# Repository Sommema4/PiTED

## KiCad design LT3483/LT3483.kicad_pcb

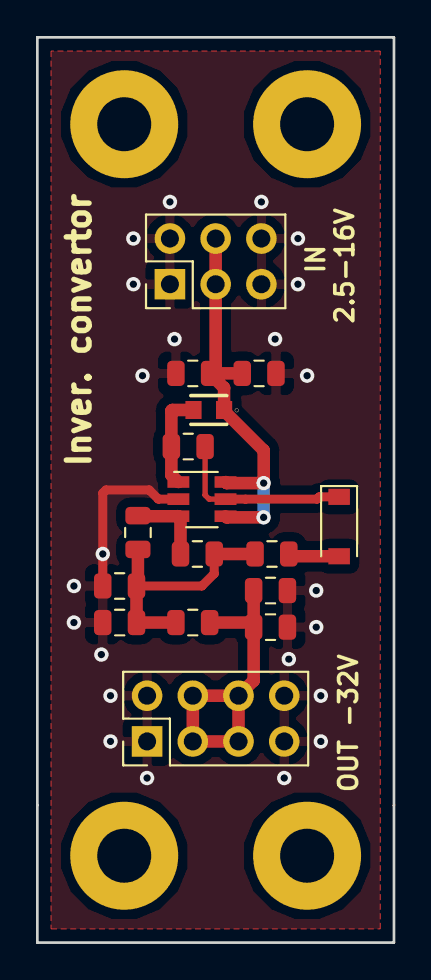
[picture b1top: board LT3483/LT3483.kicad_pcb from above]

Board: 2 copper layers, 19.8 x 50.3 mm, 20 parts (0 on the bottom side), 8 nets.

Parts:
C1: 4.7uF/30V; C_0805_2012Metric
C2: 100nF/30V; C_0805_2012Metric
C3: 0.1uF/50V; C_0805_2012Metric
C4: 5pF/50V; C_0805_2012Metric
C5, C8: 1uF/50V; C_0805_2012Metric
C6, C7: 100nF; C_0805_2012Metric
D1: MBR0540; D_SOD-123
J1: Conn_02x03_Odd_Even; PinHeader_2x03_P2.54mm_Vertical
J2: Conn_02x04_Odd_Even; PinHeader_2x04_P2.54mm_Vertical
L1: LQH2MCN100K02L
MH1: M1; MountingHole_3mm_Pad
MH2: M2; MountingHole_3mm_Pad
MH3: M3; MountingHole_3mm_Pad
MH4: M4; MountingHole_3mm_Pad
R1: 39.2R; R_0805_2012Metric
R2: 3.24M; R_0805_2012Metric
R3: 100R; R_0805_2012Metric
U1: LT3483; TSOT-23-6

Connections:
GND: C1.1, C2.1, C5.2, C6.2, C7.2, C8.2, J1.1, J1.2, J1.5, J1.6, J2.1, J2.2, J2.7, J2.8, U1.2
unnamed: C1.2, C2.2, J1.3, J1.4, L1.1, U1.4, U1.6
unnamed: C3.1, L1.2, U1.1
unnamed: C3.2, D1.1, U1.5
unnamed: C4.1, C5.1, C6.1, R1.2, R2.2, R3.2
unnamed: C4.2, R2.1, U1.3
unnamed: C7.1, C8.1, J2.3, J2.4, J2.5, J2.6, R3.1
unnamed: D1.2, R1.1

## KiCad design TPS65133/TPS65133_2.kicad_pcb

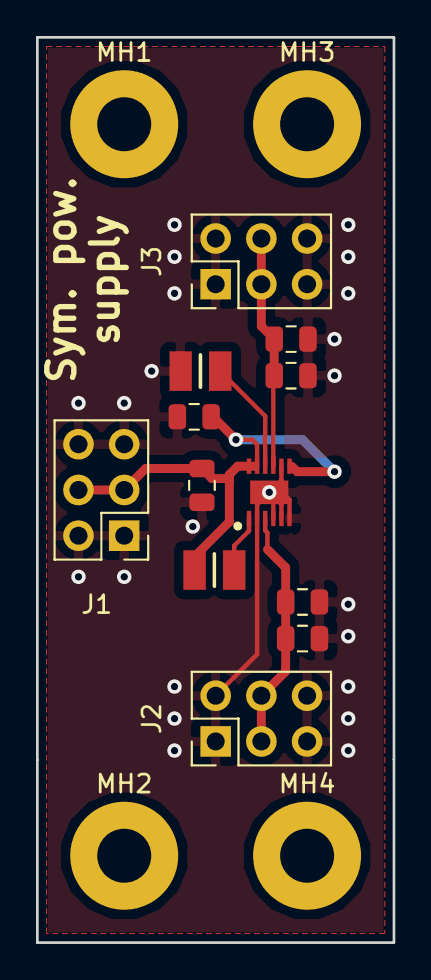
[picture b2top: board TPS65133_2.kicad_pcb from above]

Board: 2 copper layers, 19.8 x 50.3 mm, 16 parts (0 on the bottom side), 6 nets.

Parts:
C1, C5, C6: 0.1uF; C_0805_2012Metric
C2, C3, C4: 10uF; C_0805_2012Metric
IC1: TPS65133DPDR; SON45P300X300X80-13N-D
J1, J2, J3: Conn_02x03_Odd_Even; PinHeader_2x03_P2.54mm_Vertical
L1, L2: 1239AS-H-4R7M=P2
MH1, MH2, MH3, MH4: MountingHole_Pad; MountingHole_3mm_Pad

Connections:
GND: C1.2, C2.2, C3.2, C4.2, C5.2, C6.2, IC1.2, IC1.4, IC1.5, IC1.6, IC1.8, IC1.13, J1.1, J1.2, J1.5, J1.6, J2.1, J2.2, J2.5, J2.6, J3.1, J3.2, J3.5, J3.6, L2.2
unnamed: C1.1, C3.1, IC1.7, IC1.11, IC1.12, J1.3, J1.4, L1.2
unnamed: C2.1, C5.1, IC1.3, J2.3, J2.4
unnamed: C4.1, C6.1, IC1.9, J3.3, J3.4
unnamed: IC1.1, L1.1
unnamed: IC1.10, L2.1

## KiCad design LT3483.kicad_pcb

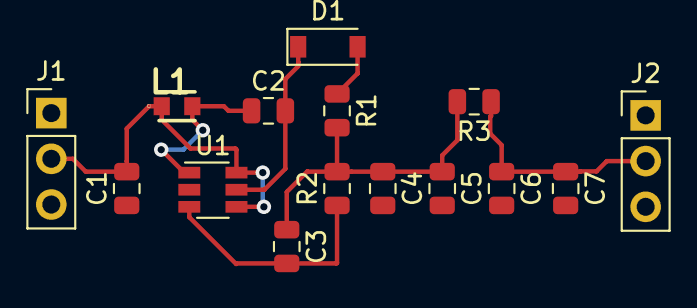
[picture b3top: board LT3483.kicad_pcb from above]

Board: 2 copper layers, 15 parts (0 on the bottom side), 8 nets.

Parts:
C1: 4.7uF/10V; C_0805_2012Metric
C2, C5, C6: 0.1uF/50V; C_0805_2012Metric
C3: 5pF/50V; C_0805_2012Metric
C4, C7: 1uF/50V; C_0805_2012Metric
D1: MBR0540; D_SOD-123
J1, J2: Conn_01x03_Male; PinHeader_1x03_P2.54mm_Vertical
L1: LQH2MCN100K02L
R1: 39R; R_0805_2012Metric
R2: 3.2M; R_0805_2012Metric
R3: 100R; R_0805_2012Metric
U1: LT3483; TSOT-23-6

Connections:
GND: C1.1, C4.2, C5.2, C6.2, C7.2, J1.1, J1.3, J2.1, J2.3, U1.2
unnamed: C1.2, J1.2, L1.1, U1.4, U1.6
unnamed: C2.1, L1.2, U1.1
unnamed: C2.2, D1.1, U1.5
unnamed: C3.1, C4.1, C5.1, R1.2, R2.2, R3.2
unnamed: C3.2, R2.1, U1.3
unnamed: C6.1, C7.1, J2.2, R3.1
unnamed: D1.2, R1.1

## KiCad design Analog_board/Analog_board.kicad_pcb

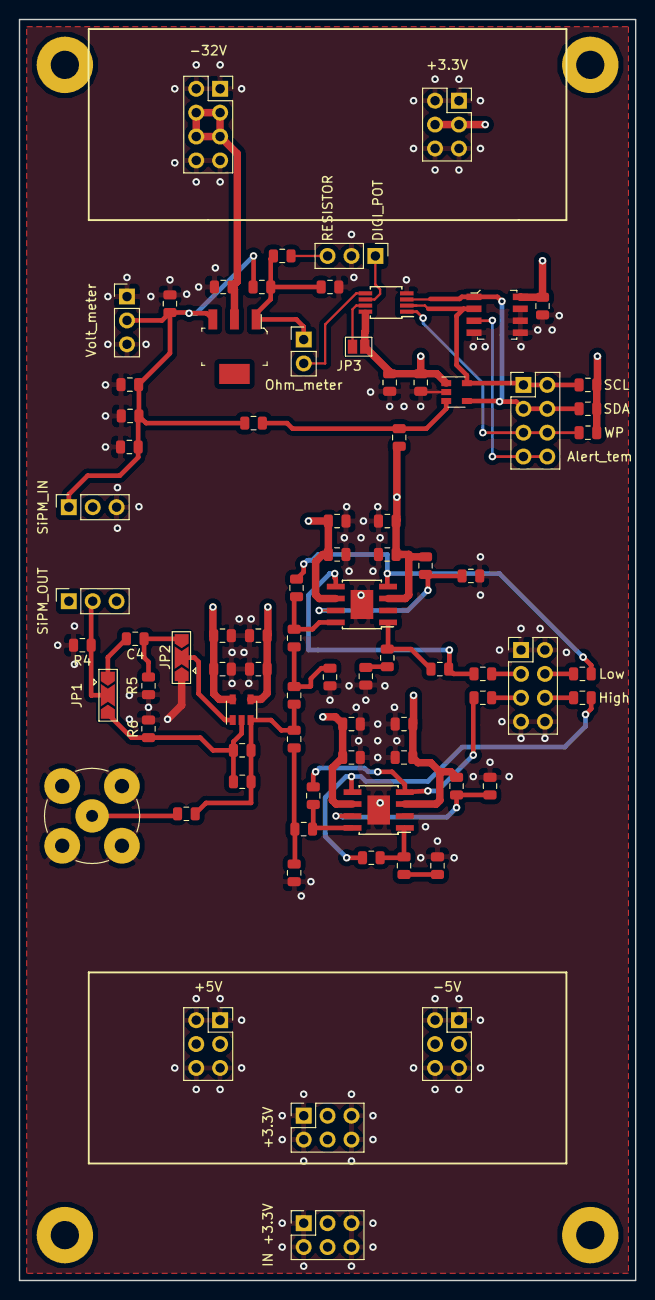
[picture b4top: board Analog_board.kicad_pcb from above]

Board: 4 copper layers, 65.5 x 134.1 mm, 85 parts (0 on the bottom side), 41 nets.

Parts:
+3.3V, +3.3V#2, +5V: 02x03_Female; PinSocket_2x03_P2.54mm_Vertical
-5V: 02x03_Female; PinSocket_2x03_P2.54mm_Vertical
-32V: 02x04_Female; PinSocket_2x04_P2.54mm_Vertical
Alert_tem: 02x04_Male; PinHeader_2x04_P2.54mm_Vertical
C1, C6, C7, C15, C17, C20, C22: 10uF; C_0805_2012Metric
C2, C11, C13: 1uF; C_0805_2012Metric
C3: 0.01uF; C_0805_2012Metric
C4: 100nF; C_0805_2012Metric
C5, C8, C14, C16, C18, C19, C21: 0.1uF; C_0805_2012Metric
C9: 3pF; C_0805_2012Metric
C10: 10uF/50V; C_0805_2012Metric
C12: 1uF/50V; C_0805_2012Metric
High: 49.9R; R_0805_2012Metric
IN +3.3V: 02x03_Female; PinSocket_2x03_P2.54mm_Vertical
J7: 02x04_Male; PinHeader_2x04_P2.54mm_Vertical
J8: Conn_Coaxial; BNC_TEConnectivity_1478204_Vertical
JP: 01x03_Male; PinHeader_1x03_P2.54mm_Vertical
JP1, JP2: Jumper_3_Open; SolderJumper-3_P2.0mm_Open_TrianglePad1.0x1.5mm
JP3: Jumper; SolderJumper-2_P1.3mm_Open_Pad1.0x1.5mm
Low: 49.9R; R_0805_2012Metric
MH1, MH2, MH3, MH4: MountingHole_Pad; MountingHole_3mm_Pad
Ohm_meter: 01x02_Male; PinHeader_1x02_P2.54mm_Vertical
R4: 10R; R_0805_2012Metric
R5, R21, R24: 1k; R_0805_2012Metric
R6: 100R; R_0805_2012Metric
R7: 464R; R_0805_2012Metric
R8: 30.1k; R_0805_2012Metric
R9: 2.67k; R_0805_2012Metric
R10: 121R; R_0805_2012Metric
R11, R29, R30: 4.02k; R_0805_2012Metric
R12: 26.1k; R_0805_2012Metric
R13, R14, R31, R32, R35: 49.9R; R_0805_2012Metric
R15: 24.9R; R_0805_2012Metric
R16: 84.5R; R_0805_2012Metric
R17: 16.5R; R_0805_2012Metric
R18: 31.6R; R_0805_2012Metric
R19, R20: 255R; R_0805_2012Metric
R22, R23: 68.1R; R_0805_2012Metric
R25, R26: 274R; R_0805_2012Metric
R27, R28: 499R; R_0805_2012Metric
SCL: 10k; R_0805_2012Metric
SDA: 10k; R_0805_2012Metric
SiPM_IN: 01x03_Female; PinSocket_1x03_P2.54mm_Vertical
SiPM_OUT: 01x03_Female; PinSocket_1x03_P2.54mm_Vertical
U2: OPA656; SOT-23-5
U3: CAT5140ZI-00-GT3; MSOP-8_3x3mm_P0.65mm
U4: TMP1075; SOIC-8_W5.3mm
U5: LM337_SOT223; SOT-223-4
U6: MCP3021; SOT-23-5
U7, U8: LMH6553; TI_SO-PowerPAD-8
Volt_meter: 01x03_Male; PinHeader_1x03_P2.54mm_Vertical
WP: 10k; R_0805_2012Metric

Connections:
+3V3: +3.3V.3, +3.3V.4, +3.3V#2.3, +3.3V#2.4, C11.1, C13.2, C14.2, IN +3.3V.3, IN +3.3V.4, JP3.1, SCL.1, SDA.1, U3.8, U4.8, U6.1, WP.1
+5V: +5V.3, +5V.4, C7.2, C8.2, C15.2, C16.2, C17.2, C18.2, R11.1, R29.2, R30.2, U2.4, U7.3, U8.3
-5V: -5V.3, -5V.4, C5.1, C6.1, C19.2, C20.2, C21.2, C22.2, U2.5, U7.6, U8.6
-36V: -32V.3, -32V.4, -32V.5, -32V.6, C10.1, U5.2
/Diff_amp/5x_out+: High.1, J7.6
/Diff_amp/5x_out-: J7.5, R35.1
/Diff_amp/SE_out: J8.1, R31.1
/Diff_amp/TIA_out: C9.1, R7.1, R13.2, R14.1, R31.2, U2.3
/Diff_amp/half_out+: J7.3, R32.1
/Diff_amp/half_out-: J7.4, Low.1
/Power_regulation/ALERT_TMP1075: Alert_tem.7, Alert_tem.8, U4.3
/Power_regulation/SCL: Alert_tem.1, Alert_tem.2, SCL.2, U3.2, U4.2, U6.5
/Power_regulation/SDA: Alert_tem.3, Alert_tem.4, SDA.2, U3.3, U4.1, U6.4
/Power_regulation/WP_digipot: Alert_tem.5, Alert_tem.6, U3.1, WP.2
GND: +3.3V.1, +3.3V.2, +3.3V.5, +3.3V.6, +3.3V#2.1, +3.3V#2.2, +3.3V#2.5, +3.3V#2.6, +5V.1, +5V.2, +5V.5, +5V.6, -5V.1, -5V.2, -5V.5, -5V.6, -32V.1, -32V.2, -32V.7, -32V.8, C1.2, C2.2, C3.2, C5.2, C6.2, C7.1, C8.1, C10.2, C11.2, C12.2, C13.1, C14.1, C15.1, C16.1, C17.1, C18.1, C19.1, C20.1, C21.1, C22.1, IN +3.3V.1, IN +3.3V.2, IN +3.3V.5, IN +3.3V.6, J7.1, J7.2, J7.7, J7.8, J8.2, JP.2, JP2.1, R4.2, R5.2, R6.2, R9.1, R15.2, R16.2, R17.2, R18.2, R21.2, R24.1, SiPM_IN.3, U3.4, U4.4, U4.5, U4.6, U4.7, U6.2, U7.2, U7.9, U8.2, U8.9, Volt_meter.1, Volt_meter.3
unnamed: C4.1, JP2.3, R5.1
unnamed: C4.2, JP1.1
unnamed: C9.2, JP1.3, R6.1, R7.2, U2.2
unnamed: JP.1, U3.6
unnamed: JP.3, R8.2
unnamed: Ohm_meter.1, R8.1, R9.2, R10.1, U5.1
unnamed: Ohm_meter.2, U3.5
unnamed: JP1.2, R4.1, SiPM_OUT.2
unnamed: JP2.2, U2.1
unnamed: JP3.2, U3.7
unnamed: R11.2, R12.1, U6.3
unnamed: R13.1, R15.1, R20.2
unnamed: R14.2, R16.1, R23.2
unnamed: R17.1, R19.2
unnamed: R18.1, R22.2
unnamed: R19.1, R25.2, U7.1
unnamed: R20.1, R26.2, U7.8
unnamed: R21.1, R30.1, U8.7
unnamed: R22.1, R27.2, U8.1
unnamed: R23.1, R28.2, U8.8
unnamed: R24.2, R29.1, U7.7
unnamed: R25.1, R32.2, U7.5
unnamed: Low.2, R26.1, U7.4
unnamed: High.2, R27.1, U8.5
unnamed: R28.1, R35.2, U8.4
VDD: C1.1, C2.1, C3.1, C12.1, R10.2, R12.2, SiPM_IN.1, U5.3, Volt_meter.2

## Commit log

2019-04-17 Create LT3483
2019-04-26 Folder LT3483
2019-05-06 TPS65133
2019-06-24 F.fab
2019-07-04 New components
2019-07-04 new component
2019-09-04 upravy, pred vyrobou, opraven problem s maskou
2019-09-05 Oprava_1.01
2019-09-06 generovani vyrobnich dat a oprava maskovani soucastky
